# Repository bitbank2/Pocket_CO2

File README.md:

# Pocket_CO2
A CH32V003 low cost pocket CO2 sensor<br>
These project files and source code are for MounRiver Studio IDE. The target device is the TSSOP20 version of the CH32V003.
<br>

<br>
The KiCad project files and gerbers (ready to produce at your favorite PCB fab) are in the PCB folder.<br>

If you find this project useful, please consider becoming a sponsor or sending a donation.

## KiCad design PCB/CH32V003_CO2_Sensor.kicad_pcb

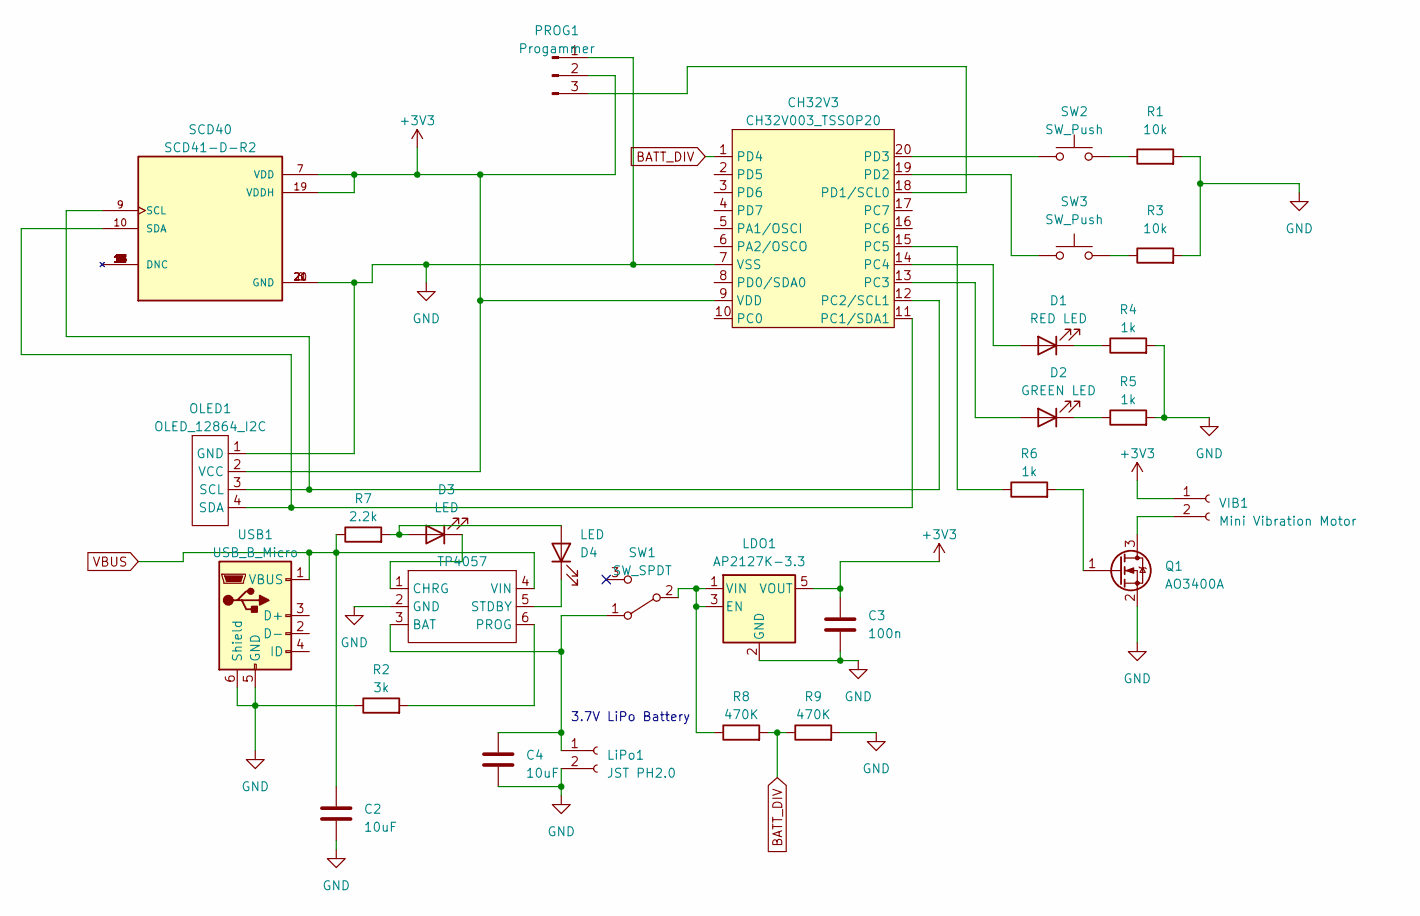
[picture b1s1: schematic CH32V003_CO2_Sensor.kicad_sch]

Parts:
C2, C4: 10uF; C_0603_1608Metric
C3: 100n; C_0603_1608Metric
CH32V3: CH32V003_TSSOP20; TSSOP-20_4.4x6.5mm_P0.65mm
D1: RED LED; LED_0603_1608Metric
D2: GREEN LED; LED_0603_1608Metric
D3, D4: LED; LED_0603_1608Metric
LDO1: AP2127K-3.3; SOT-23-5
LiPo1: JST PH2.0; JST_PH_S2B-PH-SM4-TB_1x02-1MP_P2.00mm_Horizontal
OLED1: OLED_12864_I2C; SSD1306_128x64_I2C
PROG1: Progammer; PinHeader_1x03_P2.54mm_Vertical
Q1: AO3400A; SOT-23
R1, R3: 10k; R_0603_1608Metric
R2: 3k; R_0603_1608Metric
R4, R5, R6: 1k; R_0603_1608Metric
R7: 2.2k; R_0603_1608Metric
R8, R9: 470K; R_0603_1608Metric
SCD40: SCD41-D-R2; Sensirion_SCD4x-1EP_10.1x10.1mm_P1.25mm_EP4.8x4.8mm; PARTREV 1.2
SW1: SW_SPDT; SW_SPDT_PCM12
SW2, SW3: SW_Push; SW_SPST_EVQP2
TP4057: SOT-23-6
USB1: USB_B_Micro; USB_Micro-B_Molex_47346-0001
VIB1: Mini Vibration Motor; PinSocket_1x02_P2.54mm_Vertical

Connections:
+3V3: C3.1, CH32V3.9 (VDD), LDO1.5 (VOUT), OLED1.2 (VCC), PROG1.2, SCD40.7 (VDD), SCD40.19 (VDDH), VIB1.1
BATT_DIV: CH32V3.1 (PD4), R8.2, R9.1
GND: C2.2, C3.2, C4.2, CH32V3.7 (VSS), LDO1.2 (GND), LiPo1.2, OLED1.1 (GND), PROG1.1, Q1.2 (S), R1.2, R2.1, R3.2, R4.2, R5.2, R9.2, SCD40.6 (GND), SCD40.20 (GND), SCD40.21 (GND), TP4057.2 (GND), USB1.5 (GND), USB1.6 (Shield)
unnamed: CH32V3.11 (PC1/SDA1), OLED1.4 (SDA), SCD40.10 (SDA)
unnamed: CH32V3.12 (PC2/SCL1), OLED1.3 (SCL), SCD40.9 (SCL)
unnamed: CH32V3.13 (PC3), D2.2 (A)
unnamed: CH32V3.14 (PC4), D1.2 (A)
unnamed: CH32V3.15 (PC5), R6.1
unnamed: CH32V3.18 (PD1/SCL0), PROG1.3
unnamed: CH32V3.19 (PD2), SW3.1
unnamed: CH32V3.20 (PD3), SW2.1
unnamed: D1.1 (K), R4.1
unnamed: D2.1 (K), R5.1
unnamed: D3.2 (A), D4.2 (A), R7.2
unnamed: D3.1 (K), TP4057.1 (CHRG)
unnamed: D4.1 (K), TP4057.5 (STDBY)
unnamed: LDO1.1 (VIN), LDO1.3 (EN), R8.1, SW1.2 (B)
unnamed: C4.1, LiPo1.1, SW1.1 (A), TP4057.3 (BAT)
unnamed: Q1.3 (D), VIB1.2
unnamed: Q1.1 (G), R6.2
unnamed: R1.1, SW2.2
unnamed: R3.1, SW3.2
unnamed: R2.2, TP4057.6 (PROG)
VBUS: C2.1, R7.1, TP4057.4 (VIN), USB1.1 (VBUS)

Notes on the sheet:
3.7V LiPo Battery

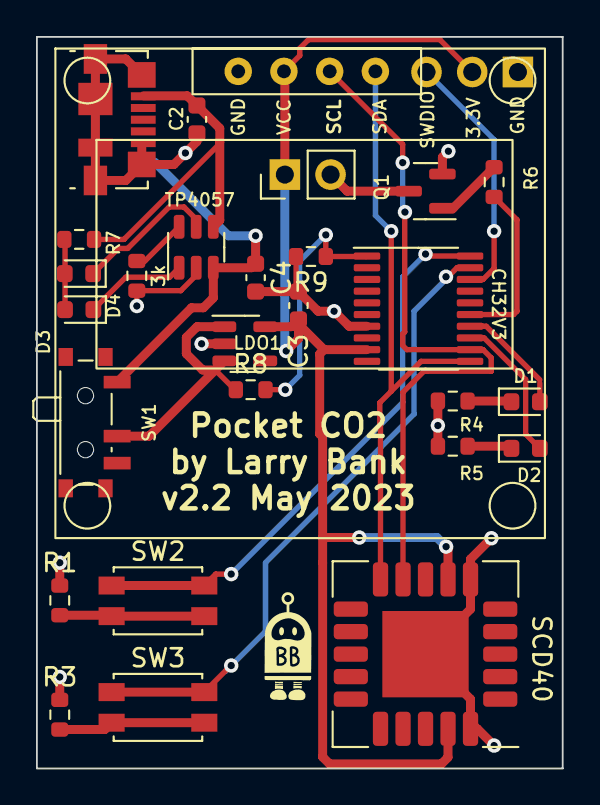
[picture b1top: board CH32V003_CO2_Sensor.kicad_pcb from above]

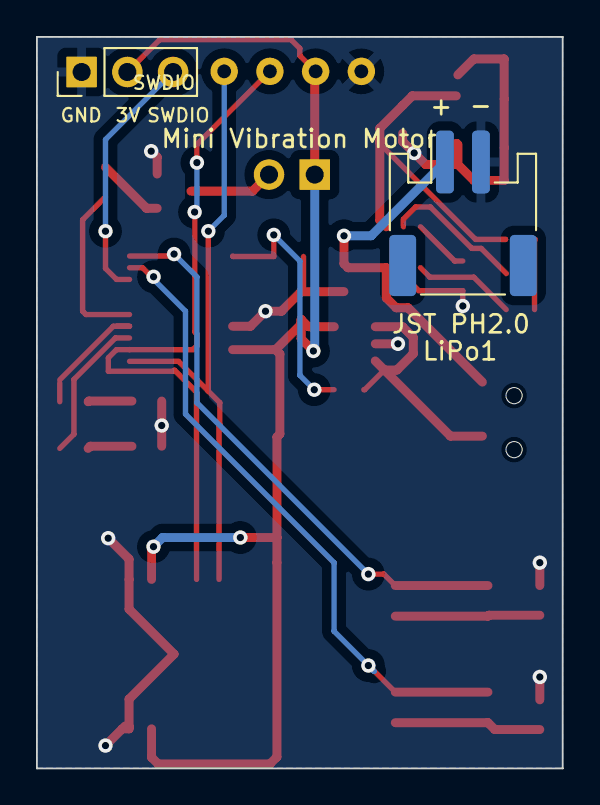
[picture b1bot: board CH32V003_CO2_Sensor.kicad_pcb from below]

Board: 2 copper layers, 29.2 x 40.6 mm, 29 parts (2 on the bottom side), 24 nets.

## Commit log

2023-04-17 Fixed low power mode and added on demand mode
2023-04-17 Added image to readme
2023-04-18 Fixed low power mode
2023-04-21 fixed display flicker and added calibration option (not working yet)
2023-04-22 first fully functional version
2023-04-24 Fixed display cleanup when CO2 changes from 4 to 3 digits
2023-04-24 Added KiCad project files and gerbers
2023-04-25 Added compiled HEX file
2023-05-21 Minor adjustments plus BOM file added
2023-06-20 Added schematic
